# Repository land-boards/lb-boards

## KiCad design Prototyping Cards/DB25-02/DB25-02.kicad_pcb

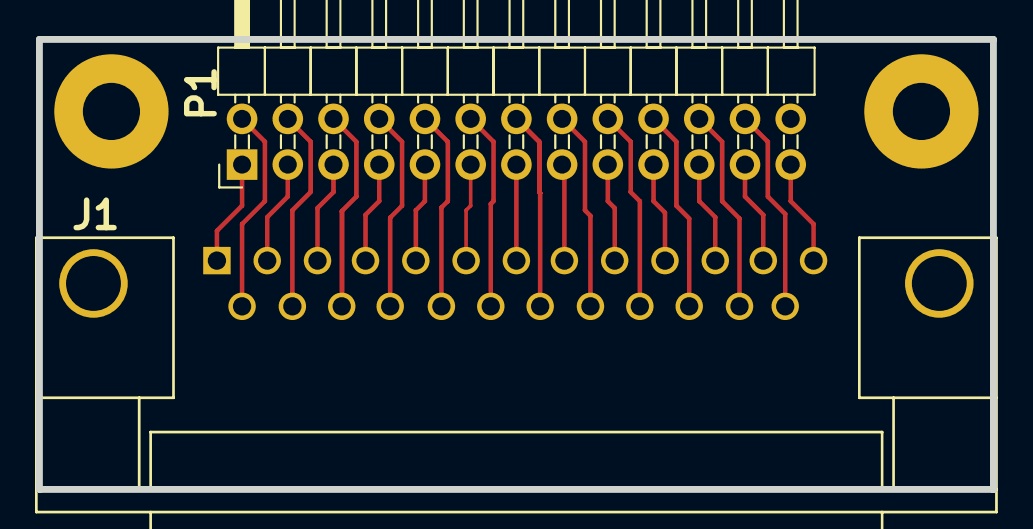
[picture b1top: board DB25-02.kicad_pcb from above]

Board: 2 copper layers, 53.0 x 25.0 mm, 5 parts (0 on the bottom side), 25 nets.

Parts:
J1: DB25; DB25MC
MTG1, MTG2: MTG_HOLE; MTG-4-40
P1: CONN_01X26; Pin_Header_Angled_2x13_Pitch2.54mm
TEST: COUPON; TEST_BLK-REAR

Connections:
unnamed: J1.1, P1.1
unnamed: J1.2, P1.3
unnamed: J1.3, P1.5
unnamed: J1.4, P1.7
unnamed: J1.5, P1.9
unnamed: J1.6, P1.11
unnamed: J1.7, P1.13
unnamed: J1.8, P1.15
unnamed: J1.9, P1.17
unnamed: J1.10, P1.19
unnamed: J1.11, P1.21
unnamed: J1.12, P1.23
unnamed: J1.13, P1.25
unnamed: J1.14, P1.2
unnamed: J1.15, P1.4
unnamed: J1.16, P1.6
unnamed: J1.17, P1.8
unnamed: J1.18, P1.10
unnamed: J1.19, P1.12
unnamed: J1.20, P1.14
unnamed: J1.21, P1.16
unnamed: J1.22, P1.18
unnamed: J1.23, P1.20
unnamed: J1.24, P1.22
unnamed: J1.25, P1.24

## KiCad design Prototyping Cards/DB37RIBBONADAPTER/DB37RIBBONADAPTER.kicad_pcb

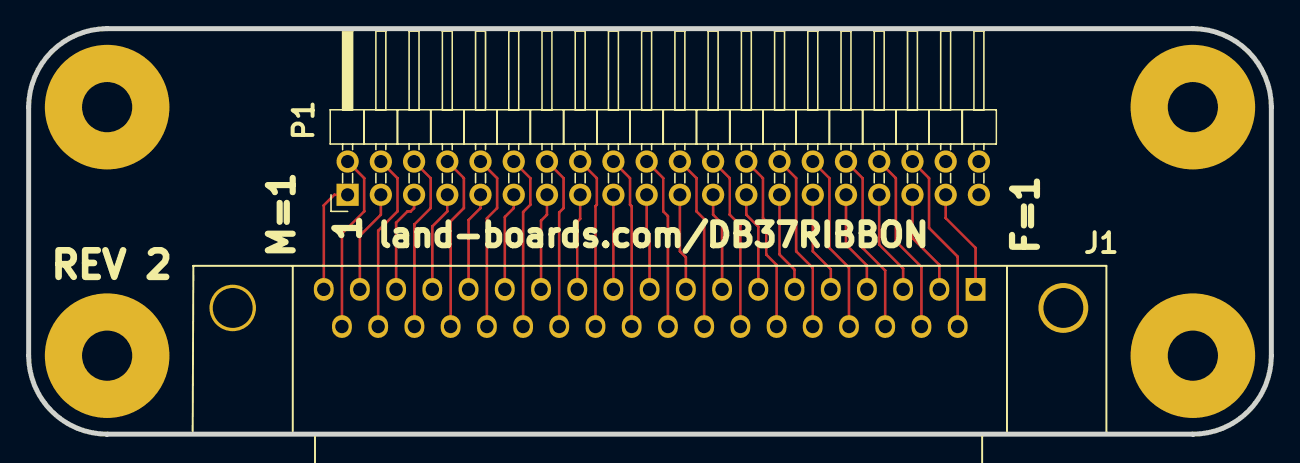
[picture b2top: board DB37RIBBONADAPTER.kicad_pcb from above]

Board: 2 copper layers, 95.0 x 31.0 mm, 7 parts (0 on the bottom side), 37 nets.

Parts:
J1: DB37; DB37FC_FIXED
MTG1, MTG2, MTG3: MTG_HOLE; MTG-6-32
MTG?1: MTG_HOLE; MTG-6-32
P1: CONN_01X40; Pin_Header_Angled_2x20_Pitch2.54mm
TEST: COUPON; TEST_BLK-REAR

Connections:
unnamed: J1.1, P1.37
unnamed: J1.2, P1.35
unnamed: J1.3, P1.33
unnamed: J1.4, P1.31
unnamed: J1.5, P1.29
unnamed: J1.6, P1.27
unnamed: J1.7, P1.25
unnamed: J1.8, P1.23
unnamed: J1.9, P1.21
unnamed: J1.10, P1.19
unnamed: J1.11, P1.17
unnamed: J1.12, P1.15
unnamed: J1.13, P1.13
unnamed: J1.14, P1.11
unnamed: J1.15, P1.9
unnamed: J1.16, P1.7
unnamed: J1.17, P1.5
unnamed: J1.18, P1.3
unnamed: J1.19, P1.1
unnamed: J1.20, P1.36
unnamed: J1.21, P1.34
unnamed: J1.22, P1.32
unnamed: J1.23, P1.30
unnamed: J1.24, P1.28
unnamed: J1.25, P1.26
unnamed: J1.26, P1.24
unnamed: J1.27, P1.22
unnamed: J1.28, P1.20
unnamed: J1.29, P1.18
unnamed: J1.30, P1.16
unnamed: J1.31, P1.14
unnamed: J1.32, P1.12
unnamed: J1.33, P1.10
unnamed: J1.34, P1.8
unnamed: J1.35, P1.6
unnamed: J1.36, P1.4
unnamed: J1.37, P1.2

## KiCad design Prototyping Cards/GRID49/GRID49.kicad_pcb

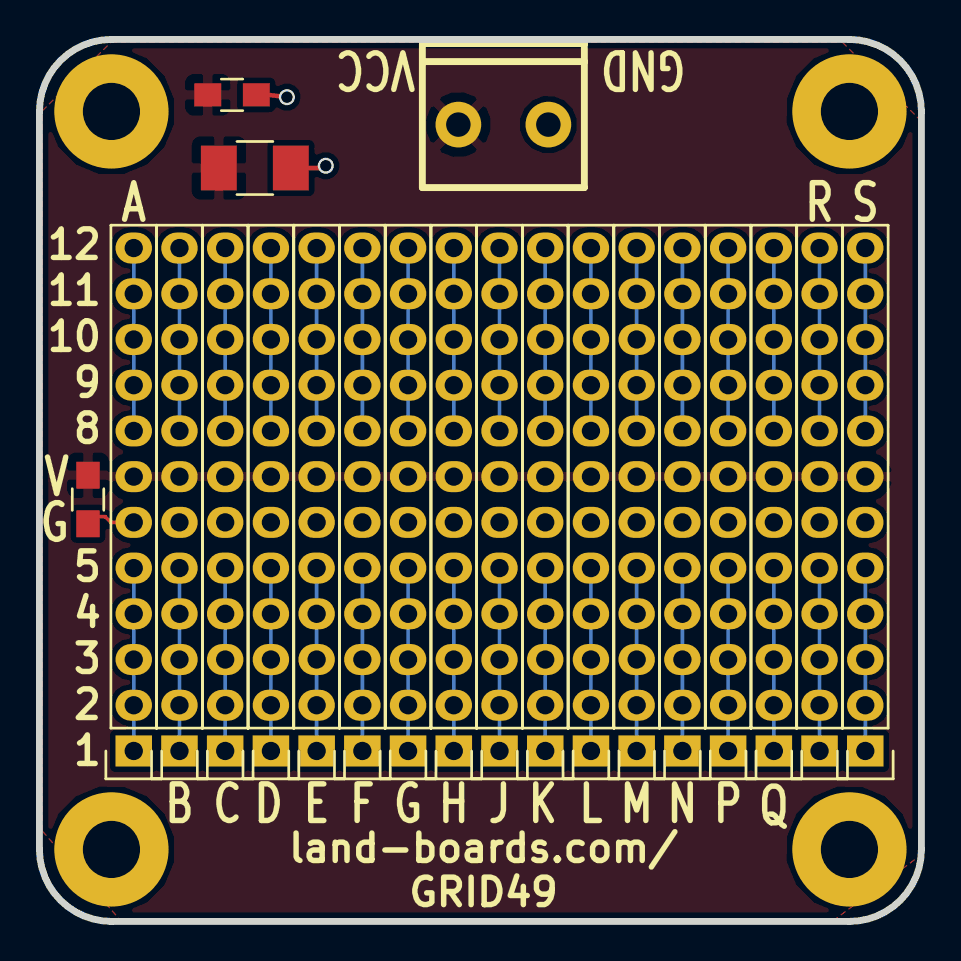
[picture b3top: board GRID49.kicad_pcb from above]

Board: 2 copper layers, 49.0 x 49.0 mm, 25 parts (0 on the bottom side), 36 nets.

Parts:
C1: 0.1uF; R_1210_HandSoldering
C2, C4: 0.1uF; R_0805_HandSoldering
H1: CONN_2; TB2-5MM
MTG1, MTG2, MTG3, MTG4: CONN_1; MTG-4-40
P1, P2, P3, P4, P5, P6, P7, P8, P9, P10, P11, P12, P13, P14, P15, P16, P17: CONN_01X12; Pin_Header_Straight_1x12

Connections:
GND: C1.2, C2.2, C4.2, H1.2, P1.6, P2.6, P3.6, P4.6, P5.6, P6.6, P7.6, P8.6, P9.6, P10.6, P11.6, P12.6, P13.6, P14.6, P15.6, P16.6, P17.6
unnamed: P1.1, P1.2, P1.3, P1.4, P1.5
unnamed: P1.8, P1.9, P1.10, P1.11, P1.12
unnamed: P2.1, P2.2, P2.3, P2.4, P2.5
unnamed: P2.8, P2.9, P2.10, P2.11, P2.12
unnamed: P3.1, P3.2, P3.3, P3.4, P3.5
unnamed: P3.8, P3.9, P3.10, P3.11, P3.12
unnamed: P4.1, P4.2, P4.3, P4.4, P4.5
unnamed: P4.8, P4.9, P4.10, P4.11, P4.12
unnamed: P5.1, P5.2, P5.3, P5.4, P5.5
unnamed: P5.8, P5.9, P5.10, P5.11, P5.12
unnamed: P6.1, P6.2, P6.3, P6.4, P6.5
unnamed: P6.8, P6.9, P6.10, P6.11, P6.12
unnamed: P7.1, P7.2, P7.3, P7.4, P7.5
unnamed: P7.8, P7.9, P7.10, P7.11, P7.12
unnamed: P8.1, P8.2, P8.3, P8.4, P8.5
unnamed: P8.8, P8.9, P8.10, P8.11, P8.12
unnamed: P9.1, P9.2, P9.3, P9.4, P9.5
unnamed: P9.8, P9.9, P9.10, P9.11, P9.12
unnamed: P10.1, P10.2, P10.3, P10.4, P10.5
unnamed: P10.8, P10.9, P10.10, P10.11, P10.12
unnamed: P11.1, P11.2, P11.3, P11.4, P11.5
unnamed: P11.8, P11.9, P11.10, P11.11, P11.12
unnamed: P12.1, P12.2, P12.3, P12.4, P12.5
unnamed: P12.8, P12.9, P12.10, P12.11, P12.12
unnamed: P13.1, P13.2, P13.3, P13.4, P13.5
unnamed: P13.8, P13.9, P13.10, P13.11, P13.12
unnamed: P14.1, P14.2, P14.3, P14.4, P14.5
unnamed: P14.8, P14.9, P14.10, P14.11, P14.12
unnamed: P15.1, P15.2, P15.3, P15.4, P15.5
unnamed: P15.8, P15.9, P15.10, P15.11, P15.12
unnamed: P16.1, P16.2, P16.3, P16.4, P16.5
unnamed: P16.8, P16.9, P16.10, P16.11, P16.12
unnamed: P17.1, P17.2, P17.3, P17.4, P17.5
unnamed: P17.8, P17.9, P17.10, P17.11, P17.12
VCC: C1.1, C2.1, C4.1, H1.1, P1.7, P2.7, P3.7, P4.7, P5.7, P6.7, P7.7, P8.7, P9.7, P10.7, P11.7, P12.7, P13.7, P14.7, P15.7, P16.7, P17.7

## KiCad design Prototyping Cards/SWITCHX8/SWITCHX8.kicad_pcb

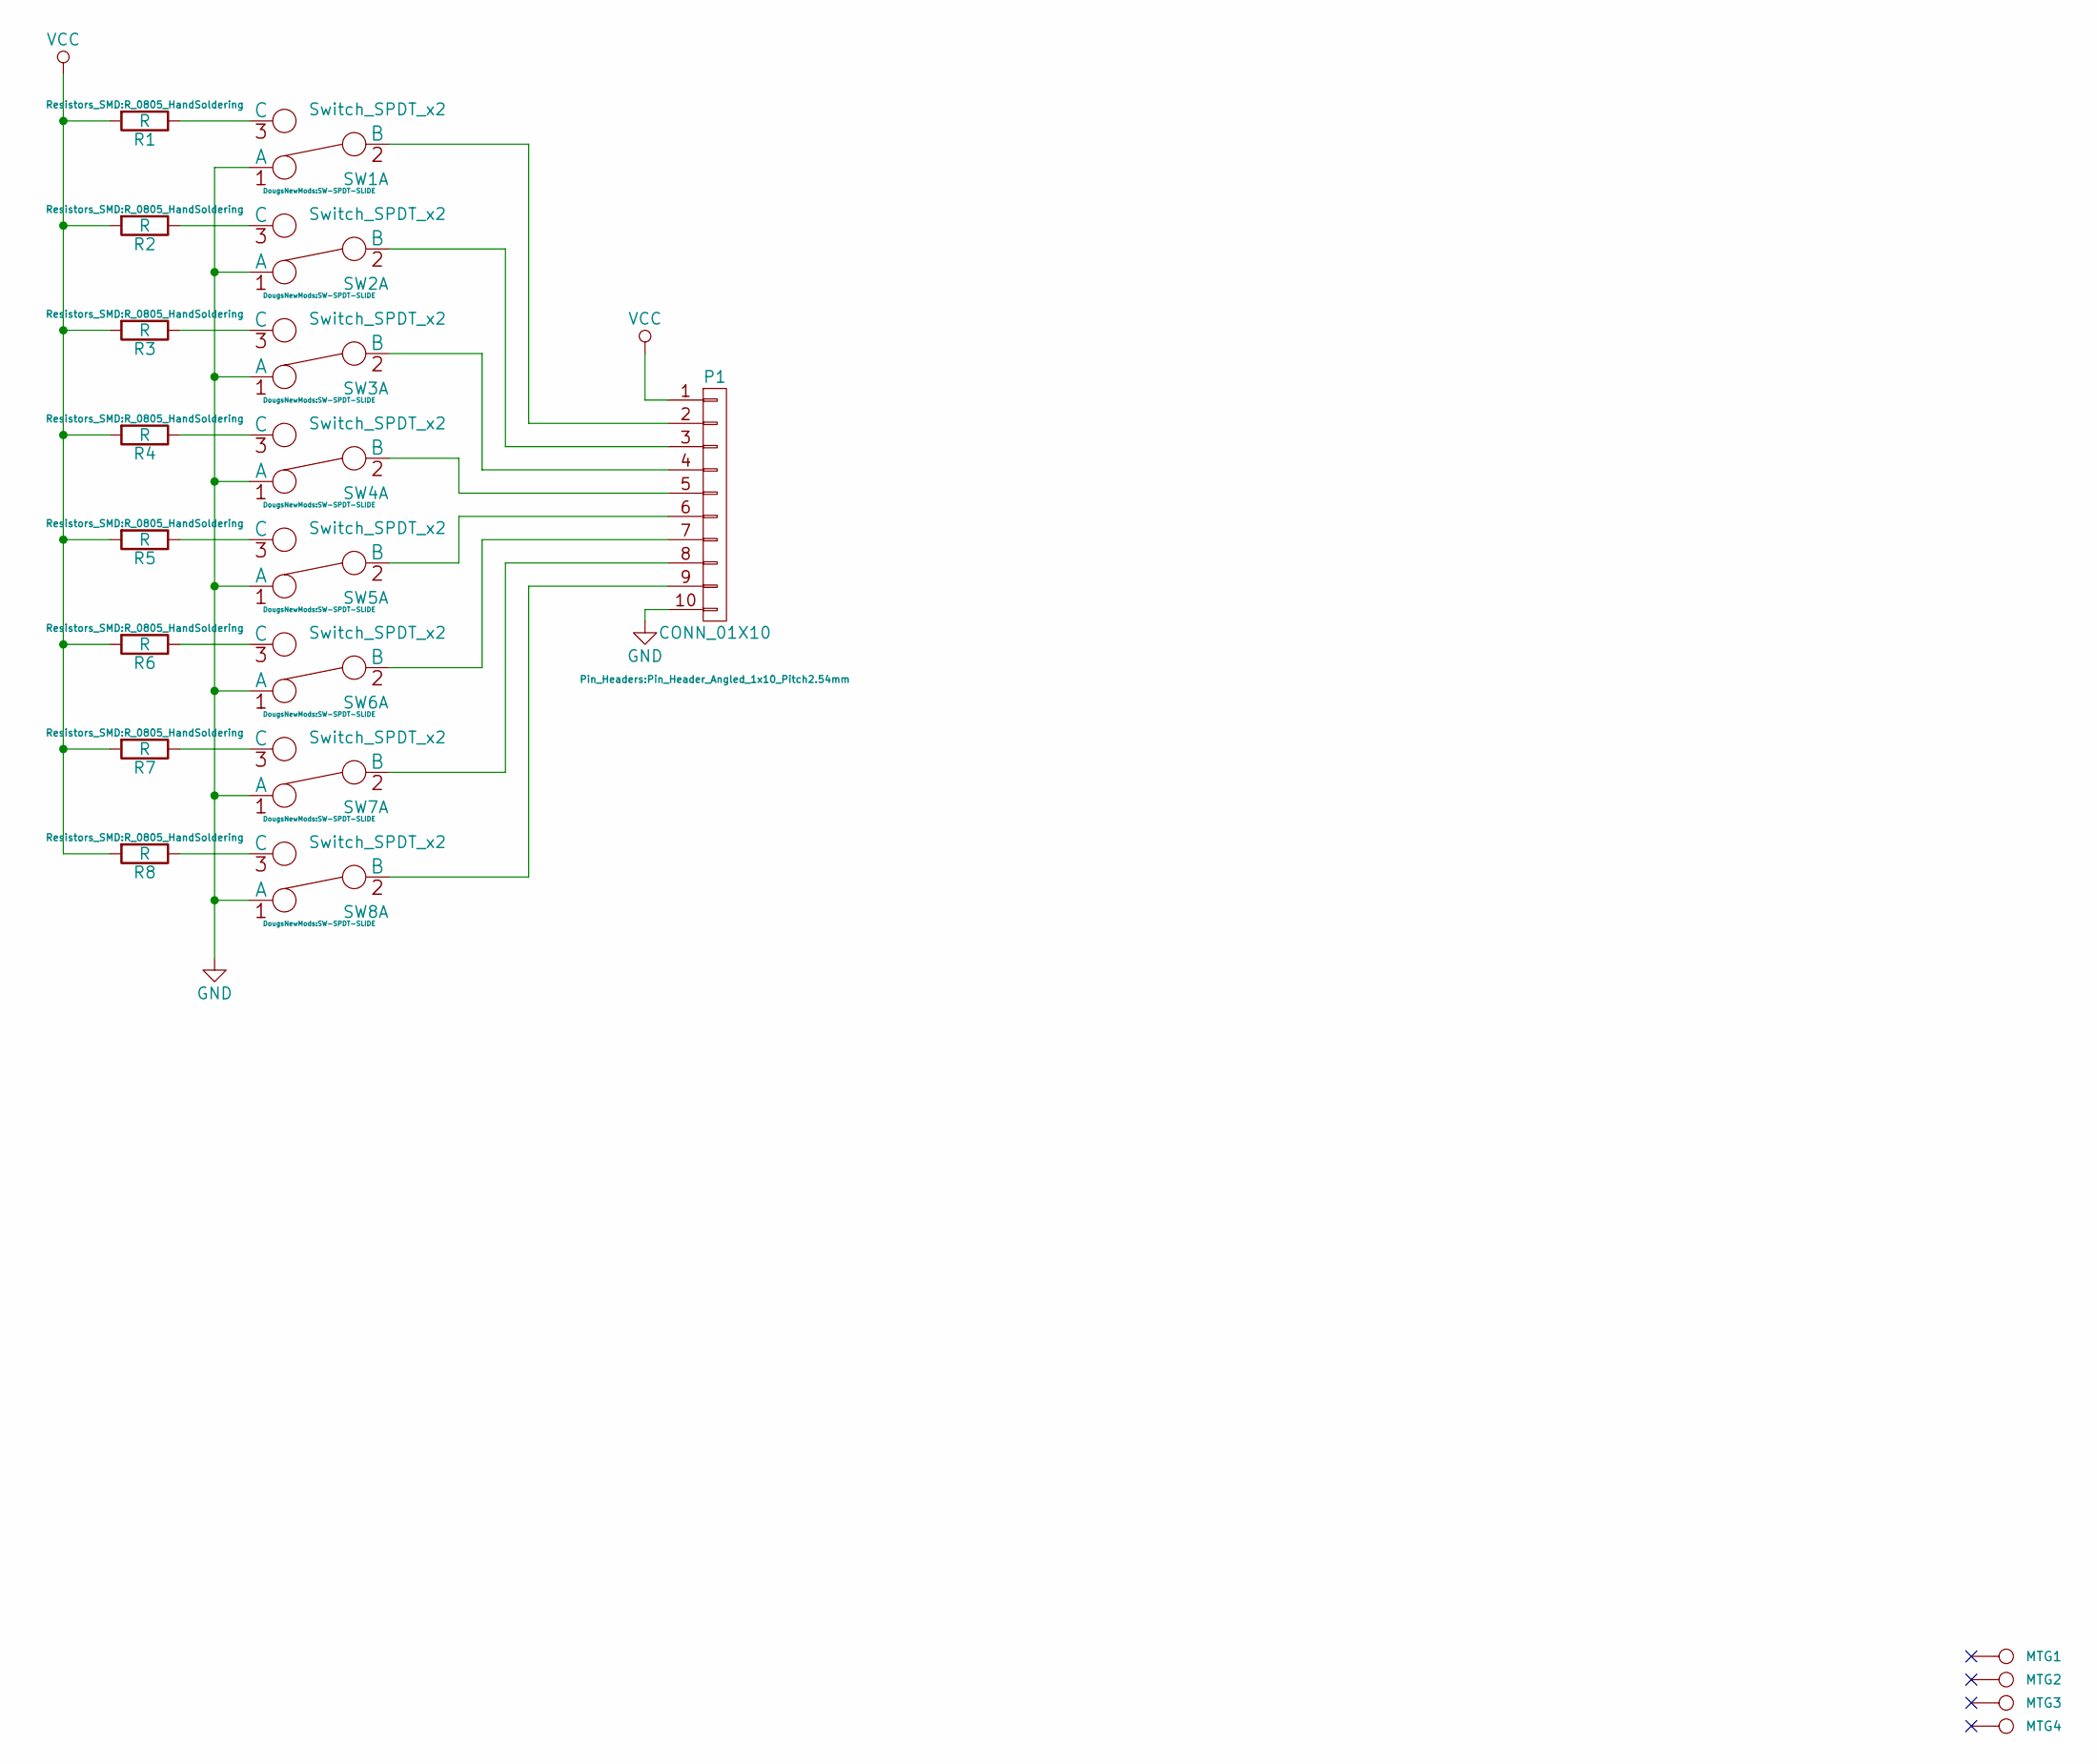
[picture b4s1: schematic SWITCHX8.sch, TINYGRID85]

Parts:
MTG1, MTG2, MTG3, MTG4: CONN_1; MTG-4-40
P1: CONN_01X10; Pin_Header_Angled_1x10_Pitch2.54mm
R1, R2, R3, R4, R5, R6, R7, R8: R; R_0805_HandSoldering
SW1, SW2, SW3, SW4, SW5, SW6, SW7, SW8: Switch_SPDT_x2; SW-SPDT-SLIDE

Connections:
GND: P1.10, SW1.1 (A), SW2.1 (A), SW3.1 (A), SW4.1 (A), SW5.1 (A), SW6.1 (A), SW7.1 (A), SW8.1 (A)
unnamed: P1.2, SW1.2 (B)
unnamed: P1.3, SW2.2 (B)
unnamed: P1.4, SW3.2 (B)
unnamed: P1.5, SW4.2 (B)
unnamed: P1.6, SW5.2 (B)
unnamed: P1.7, SW6.2 (B)
unnamed: P1.8, SW7.2 (B)
unnamed: P1.9, SW8.2 (B)
unnamed: R1.1, SW1.3 (C)
unnamed: R2.1, SW2.3 (C)
unnamed: R3.1, SW3.3 (C)
unnamed: R4.1, SW4.3 (C)
unnamed: R5.1, SW5.3 (C)
unnamed: R6.1, SW6.3 (C)
unnamed: R7.1, SW7.3 (C)
unnamed: R8.1, SW8.3 (C)
VCC: P1.1, R1.2, R2.2, R3.2, R4.2, R5.2, R6.2, R7.2, R8.2

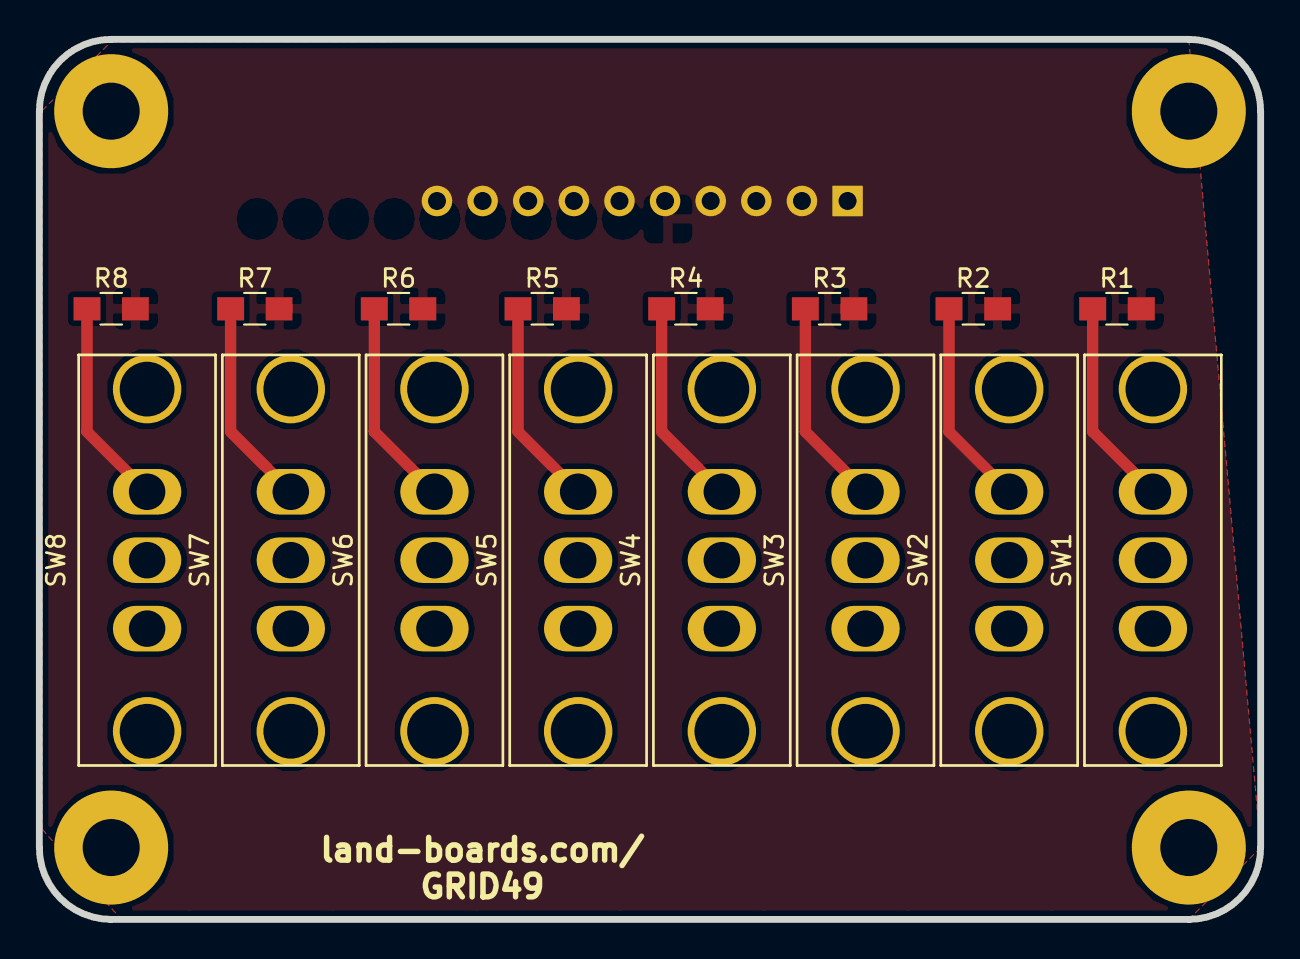
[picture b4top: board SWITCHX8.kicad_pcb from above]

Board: 2 copper layers, 68.0 x 49.0 mm, 21 parts (1 on the bottom side), 18 nets.

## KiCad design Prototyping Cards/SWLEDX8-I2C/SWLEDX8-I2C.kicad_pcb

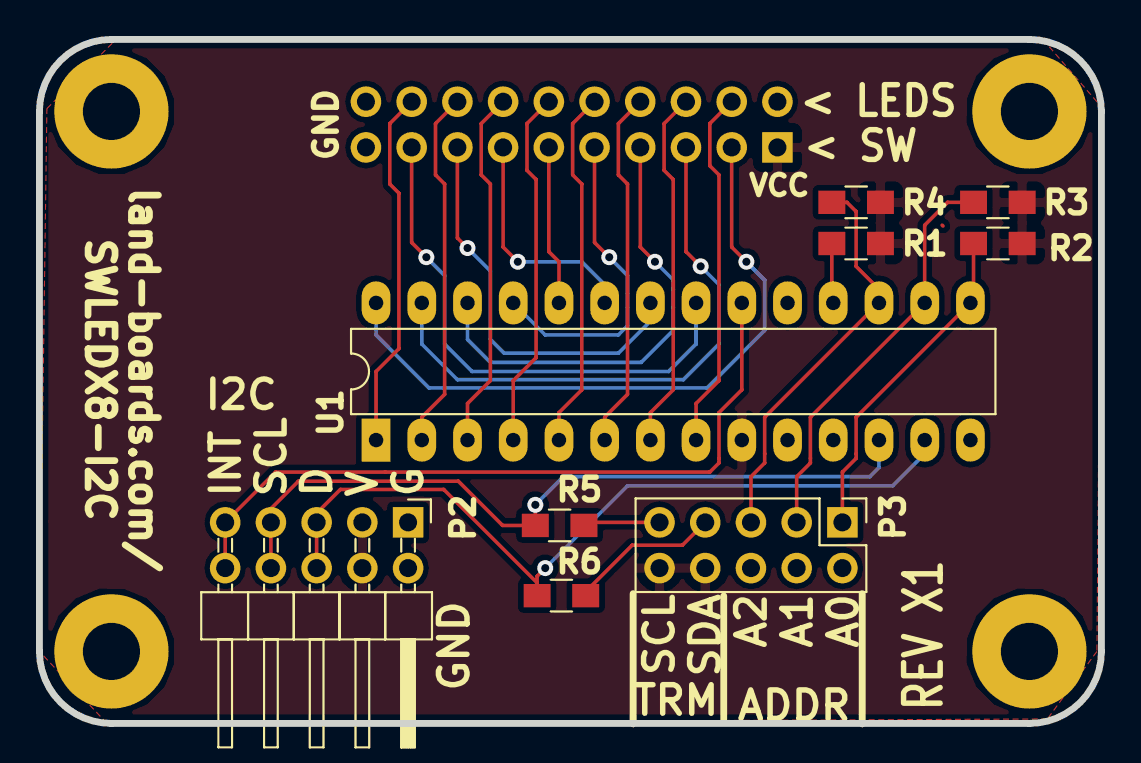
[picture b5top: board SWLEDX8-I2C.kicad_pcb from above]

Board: 2 copper layers, 59.0 x 38.0 mm, 14 parts (1 on the bottom side), 27 nets.

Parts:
MTG1, MTG2, MTG3: MTG_HOLE; MTG-4-40
MTG?1: MTG_HOLE; MTG-4-40
P1: CONN_02X10; Pin_Header_Angled_2x10_Pitch2.54mm
P2: CONN_02X05; Pin_Header_Angled_2x05_Pitch2.54mm
P3: CONN_02X05; Pin_Header_Straight_2x05_Pitch2.54mm
R1, R2, R3, R4: 10K; R_0805_HandSoldering
R5, R6: 2.2K; R_0805_HandSoldering
U1: MCP23017P; DIP-28_W7.62mm_LongPads

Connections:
/A0: P3.1, R2.2, U1.15
/A1: P3.3, R3.2, U1.16
/A2: P3.5, R4.2, U1.17
/INTS: P2.9, P2.10, U1.20
/L0: P1.4, U1.8
/L1: P1.6, U1.7
/L2: P1.8, U1.6
/L3: P1.10, U1.5
/L4: P1.12, U1.4
/L5: P1.14, U1.3
/L6: P1.16, U1.2
/L7: P1.18, U1.1
/RST: R1.2, U1.18
/S0: P1.3, U1.28
/S1: P1.5, U1.27
/S2: P1.7, U1.26
/S3: P1.9, U1.25
/S4: P1.11, U1.24
/S5: P1.13, U1.23
/S6: P1.15, U1.22
/S7: P1.17, U1.21
/SCL: P2.7, P2.8, R5.1, U1.12
/SDA: P2.5, P2.6, R6.1, U1.13
GND: P1.19, P1.20, P2.1, P2.2, P3.2, P3.4, P3.6, U1.10
unnamed: P3.7, R6.2
unnamed: P3.9, R5.2
VCC: P1.1, P2.3, P2.4, P3.8, P3.10, R1.1, R2.1, R3.1, R4.1, U1.9

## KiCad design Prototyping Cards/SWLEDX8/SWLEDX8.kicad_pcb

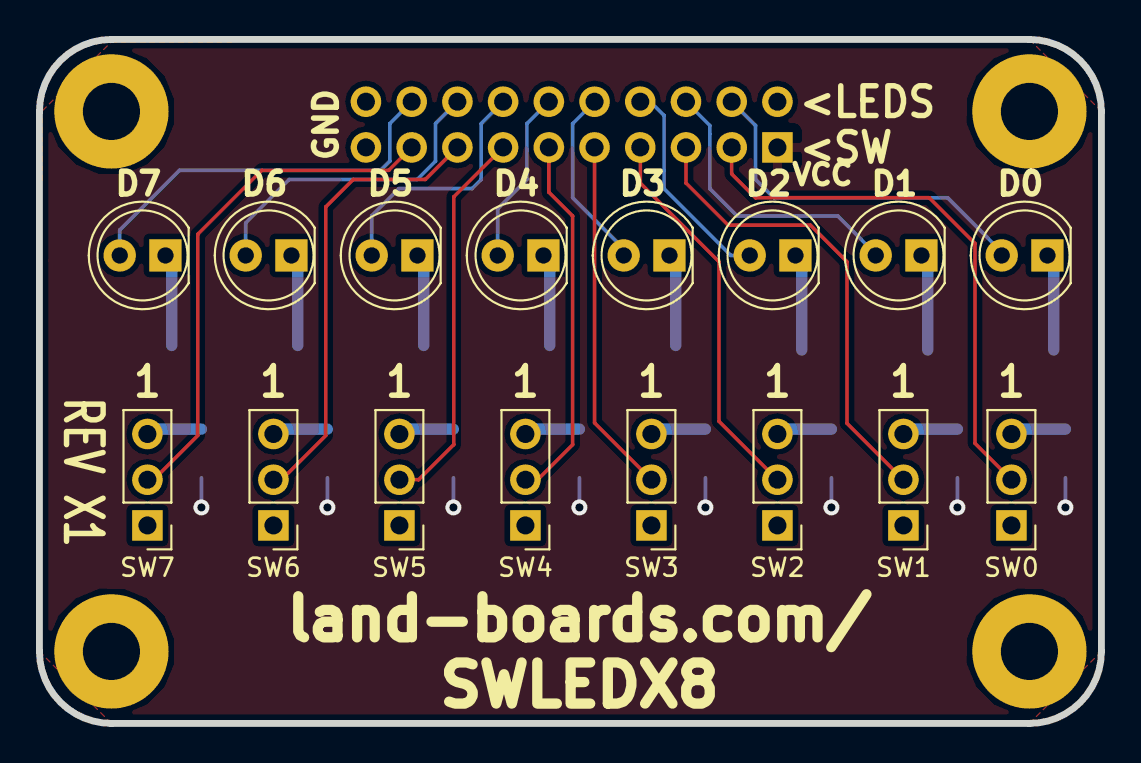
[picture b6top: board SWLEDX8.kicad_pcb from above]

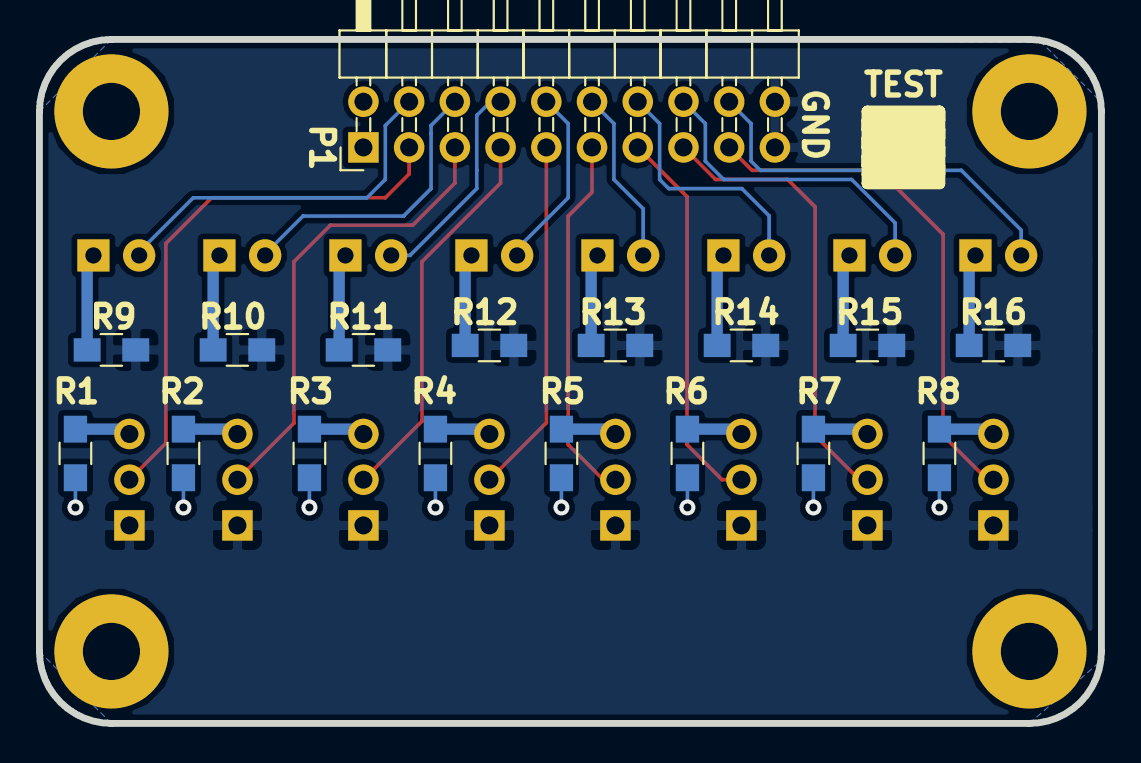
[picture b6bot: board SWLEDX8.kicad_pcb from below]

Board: 2 copper layers, 59.0 x 38.0 mm, 38 parts (17 on the bottom side), 34 nets.

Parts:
D0, D1, D2, D3, D4, D5, D6, D7: LED-fixed; LED_D5.0mm
MTG1, MTG2, MTG3: MTG_HOLE; MTG-4-40
MTG?1: MTG_HOLE; MTG-4-40
P1: CONN_02X10; Pin_Header_Angled_2x10_Pitch2.54mm
R1, R2, R3, R4, R5, R6, R7, R8, R9, R10, R11, R12, R13, R14, R15, R16: R; R_0805_HandSoldering
SW0, SW1, SW2, SW3, SW4, SW5, SW6, SW7: Switch_SPDT_x2; Pin_Header_Straight_1x03_Pitch2.54mm
TEST: COUPON; TEST_BLK-REAR

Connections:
/L0: D0.2, P1.4
/L1: D1.2, P1.6
/L2: D2.2, P1.8
/L3: D3.2, P1.10
/L4: D4.2, P1.12
/L5: D5.2, P1.14
/L6: D6.2, P1.16
/L7: D7.2, P1.18
/S0: P1.3, SW0.2
/S1: P1.5, SW1.2
/S2: P1.7, SW2.2
/S3: P1.9, SW3.2
/S4: P1.11, SW4.2
/S5: P1.13, SW5.2
/S6: P1.15, SW6.2
/S7: P1.17, SW7.2
GND: P1.19, P1.20, R9.1, R10.1, R11.1, R12.1, R13.1, R14.1, R15.1, R16.1, SW0.1, SW1.1, SW2.1, SW3.1, SW4.1, SW5.1, SW6.1, SW7.1
unnamed: D0.1, R9.2
unnamed: D1.1, R10.2
unnamed: D2.1, R11.2
unnamed: D3.1, R12.2
unnamed: D4.1, R13.2
unnamed: D5.1, R14.2
unnamed: D6.1, R15.2
unnamed: D7.1, R16.2
unnamed: R1.1, SW0.3
unnamed: R2.1, SW1.3
unnamed: R3.1, SW2.3
unnamed: R4.1, SW3.3
unnamed: R5.1, SW4.3
unnamed: R6.1, SW5.3
unnamed: R7.1, SW6.3
unnamed: R8.1, SW7.3
VCC: P1.1, R1.2, R2.2, R3.2, R4.2, R5.2, R6.2, R7.2, R8.2

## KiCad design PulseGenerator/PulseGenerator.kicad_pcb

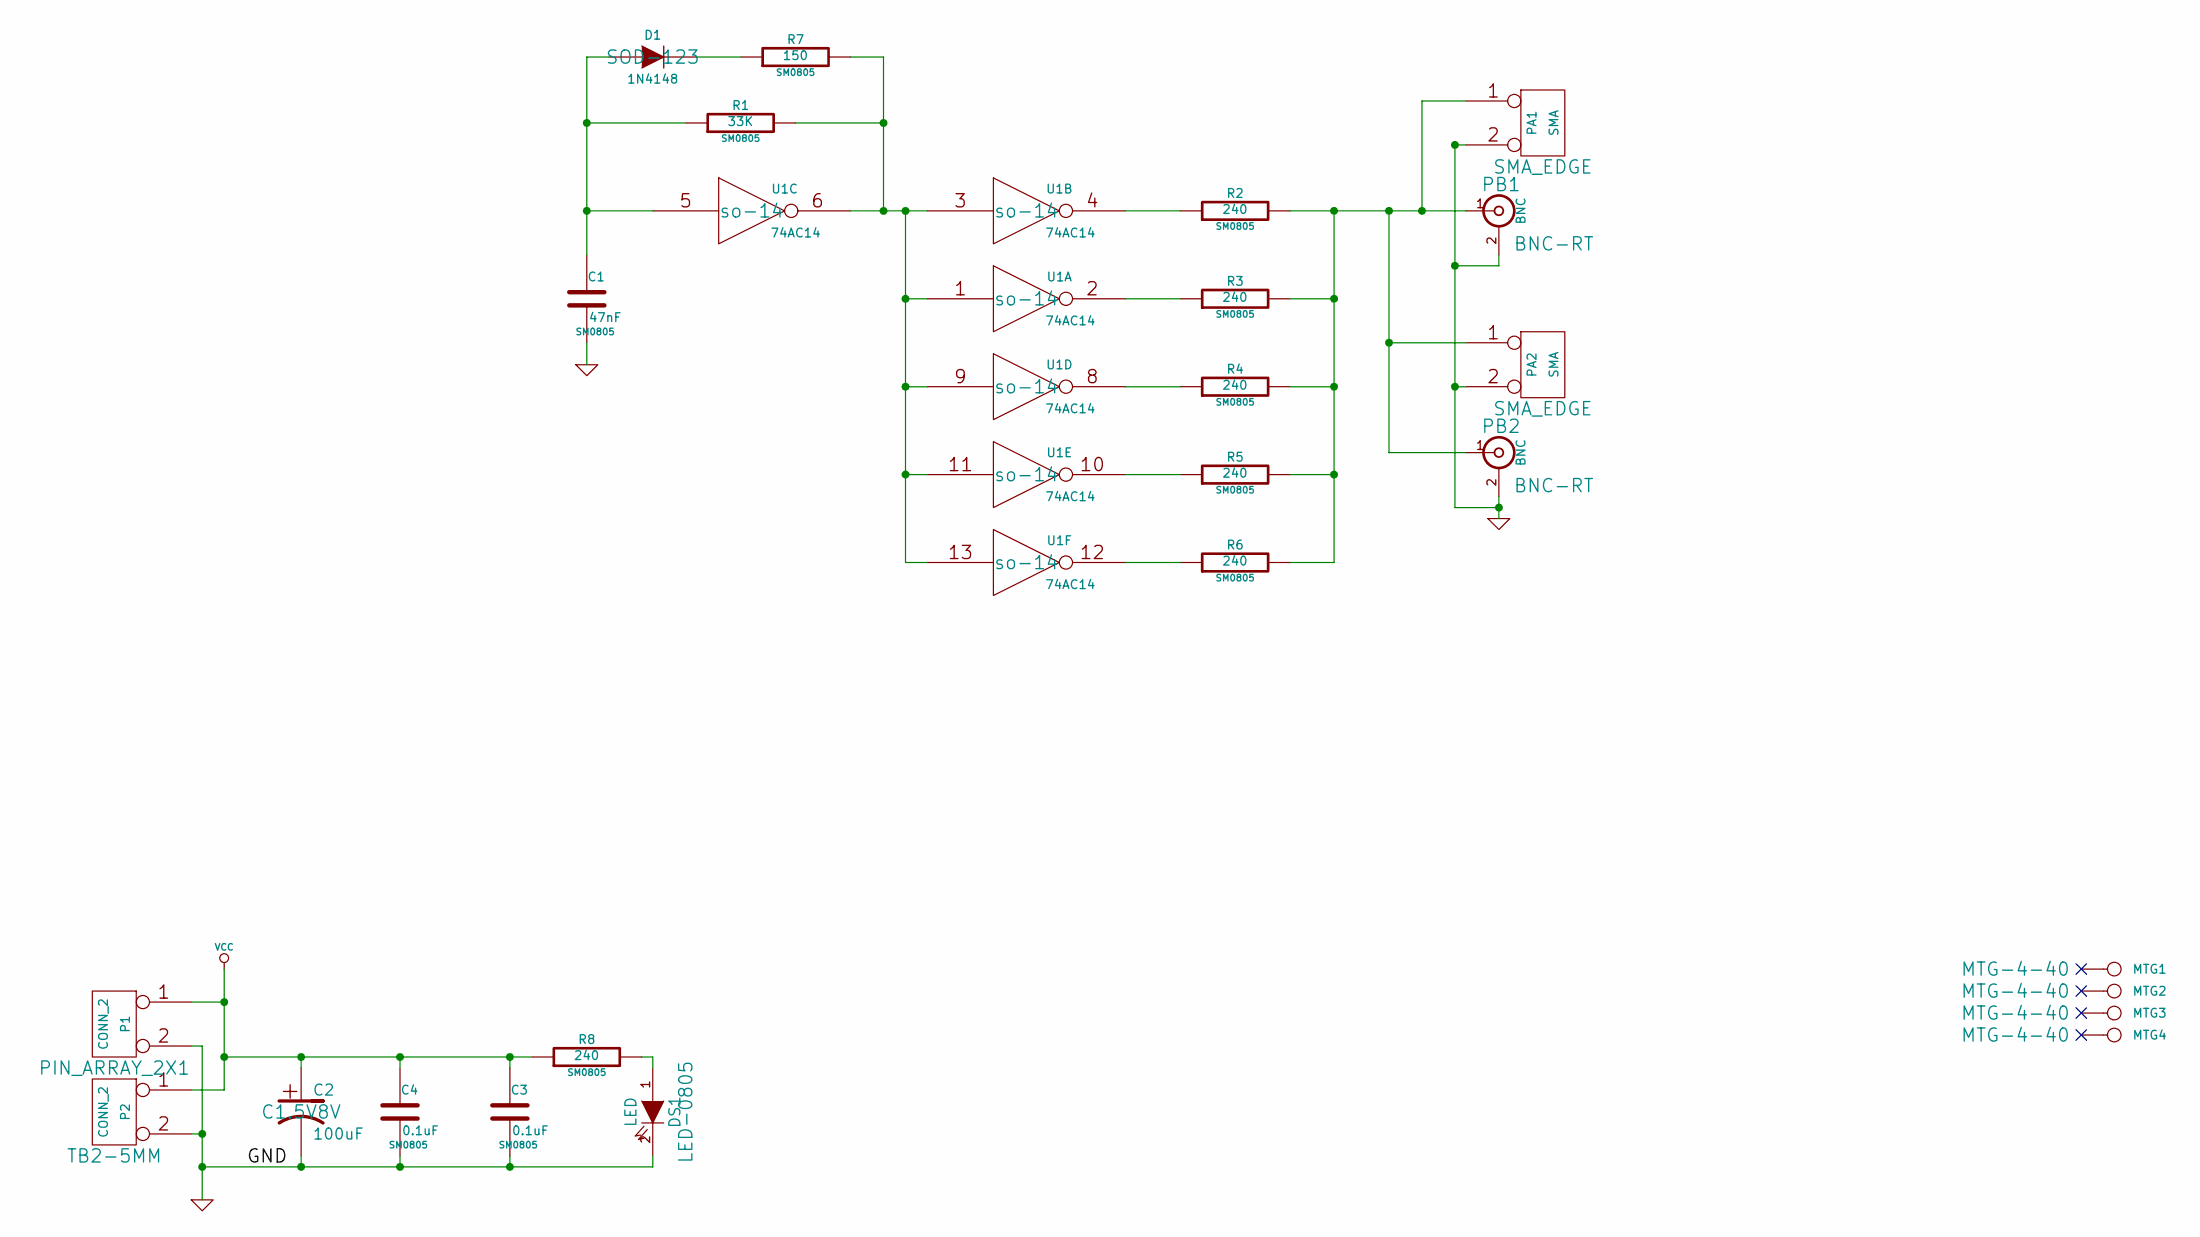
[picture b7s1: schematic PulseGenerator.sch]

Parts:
C1: 47nF; SM0805
C2: 100uF; C1.5V8V
C3, C4: 0.1uF; SM0805
D1: 1N4148; SOD-123
DS1: LED; LED-0805
MTG1, MTG2, MTG3, MTG4: CONN_1; MTG-4-40
P1: CONN_2; PIN_ARRAY_2X1
P2: CONN_2; TB2-5MM
PA1, PA2: SMA; SMA_EDGE
PB1, PB2: BNC; BNC-RT
R1: 33K; SM0805
R2, R3, R4, R5, R6, R8: 240; SM0805
R7: 150; SM0805
U1: 74AC14; so-14

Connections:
GND: C1.2, C2.2, C3.2, C4.2, DS1.2 (K), P1.2 (PM), P2.2 (PM), PA1.2 (PM), PA2.2 (PM), PB1.2 (Ext), PB2.2 (Ext), U1.7 (GND)
unnamed: DS1.1 (A), R8.2
unnamed: D1.2 (K), R7.1
unnamed: C1.1, D1.1 (A), R1.1, U1.5
unnamed: R2.1, U1.4
unnamed: R3.1, U1.2
unnamed: R1.2, R7.2, U1.1, U1.3, U1.6, U1.9, U1.11, U1.13
unnamed: PA1.1, PA2.1, PB1.1 (In), PB2.1 (In), R2.2, R3.2, R4.2, R5.2, R6.2
unnamed: R4.1, U1.8
unnamed: R5.1, U1.10
unnamed: R6.1, U1.12
VCC: C2.1, C3.1, C4.1, P1.1, P2.1, R8.1, U1.14 (VCC)

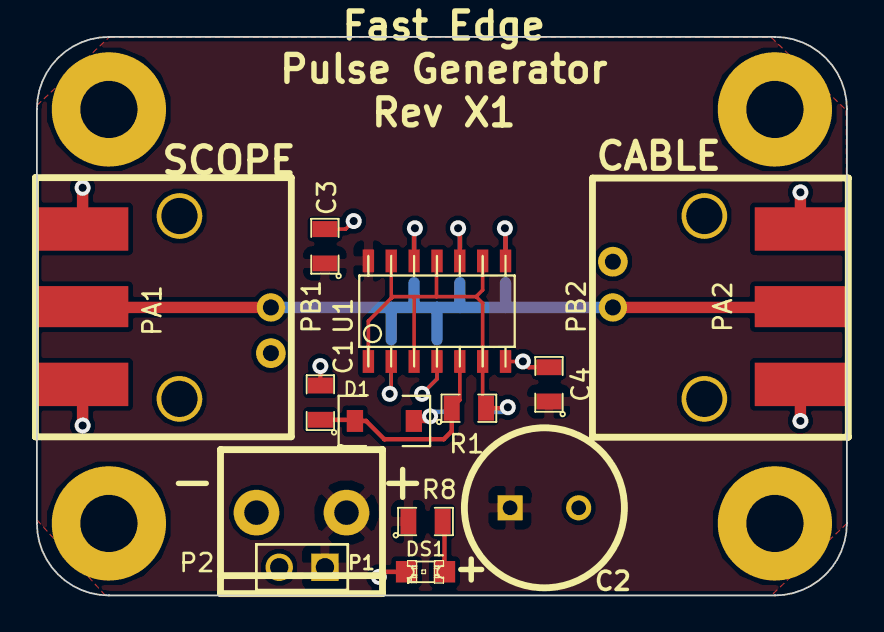
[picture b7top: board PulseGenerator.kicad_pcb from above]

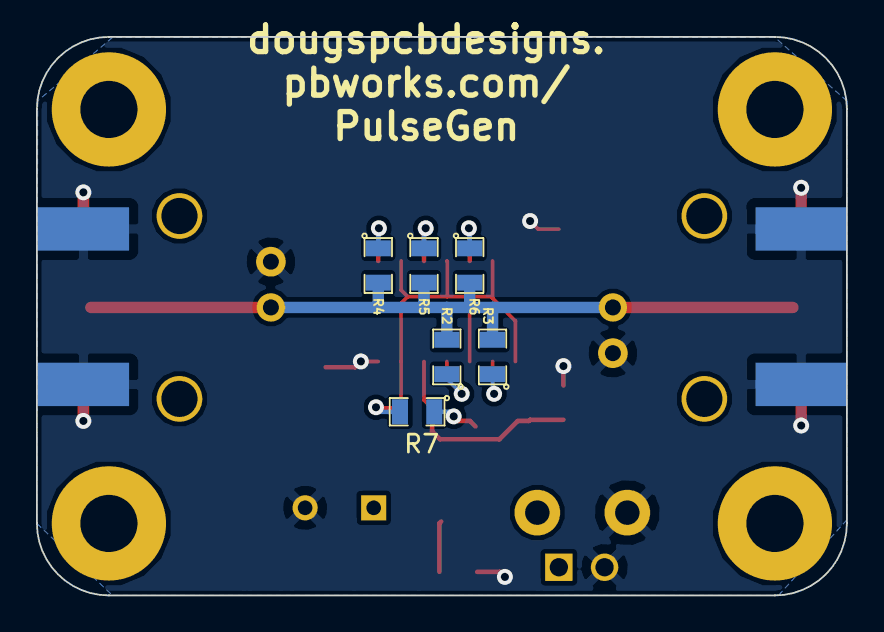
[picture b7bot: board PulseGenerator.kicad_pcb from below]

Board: 2 copper layers, 45.0 x 31.0 mm, 25 parts (6 on the bottom side), 12 nets.
